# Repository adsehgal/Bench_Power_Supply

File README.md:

<!--  -->

# _Bench Power Supply PCB_

This repo contains project files for a bench top power supply I designed for my home lab.

## _Requirements:_

- **Small** for crammed work spaces
- **Adjustable** and designed to **store values** on each power cycle
- **2 layer** board - V2.0 bumped to 4 layer
- **Digitally controlled** - no mechanical parts
- Clear **annunciators**
- Uses an external AC-DC converter
- At least a **2A max** load
- Cover most logic levels
- _Possibly have preset buttons_

## Built With:

#### V1.0:

- [KiCad](https://kicad-pcb.org/) - Schematic capture and layout V1.0
- [VS Code | PlatformIO](https://code.visualstudio.com/) - Used to develop firmware V1.0
- [Fusion 360](https://www.autodesk.com/education/edu-software/overview) - Used to design 3-D models for packages

#### V2.0:

- [Altium Designer](https://www.altium.com/) - Schematic capture and layout V2.0
- [STM32CubeIDE](https://www.st.com/en/development-tools/stm32cubeide.html) - Used to develop firmware V2.0

## Notes:

- The PCB uses a 5/5mil DRC constraint
- The top of the PCB acts as the product face plate

## Firmware Changes:

| Change Type          | V 1.0     | V2.0       |
| -------------------- | --------- | ---------- |
| MCU Architecture     | 8-bit AVR | 32-bit ARM |
| User Input Handling  | Polling   | Interrupts |
| Analog Readings      | Polling   | DMA        |
| Serial Communication | None      | Added      |
| Operating System     | None      | FREERTOS   |
|                      |           |            |

## Hardware Changes:

| Change Type       | V 1.0             | V2.0              |
| ----------------- | ----------------- | ----------------- |
| MCU Selection     | ATMega 328p       | STM32F401RB       |
| Digi Pot          | MCP4023 - Up/Down | MCP4018 - I2C     |
| Inductor Seletion | 4.7µH - 7A        | 4.7µH - 4A        |
| PCB Stackup       | 2-layer           | 4-layer           |
| User Input Buffer | None              | Schmitt triggered |
| Analog Buffers    | LM358 - Not RRIO  | TLV271 - RRIO     |
| MCU VDD           | Not always on     | Always On         |
| OLED Reset        | None              | Added             |
|                   |                   |                   |

## Authors

- **Aditya Sehgal** - _PCB Layout, Firmware, 3-D Modelling_ - [Adsehgal](https://github.com/adsehgal)

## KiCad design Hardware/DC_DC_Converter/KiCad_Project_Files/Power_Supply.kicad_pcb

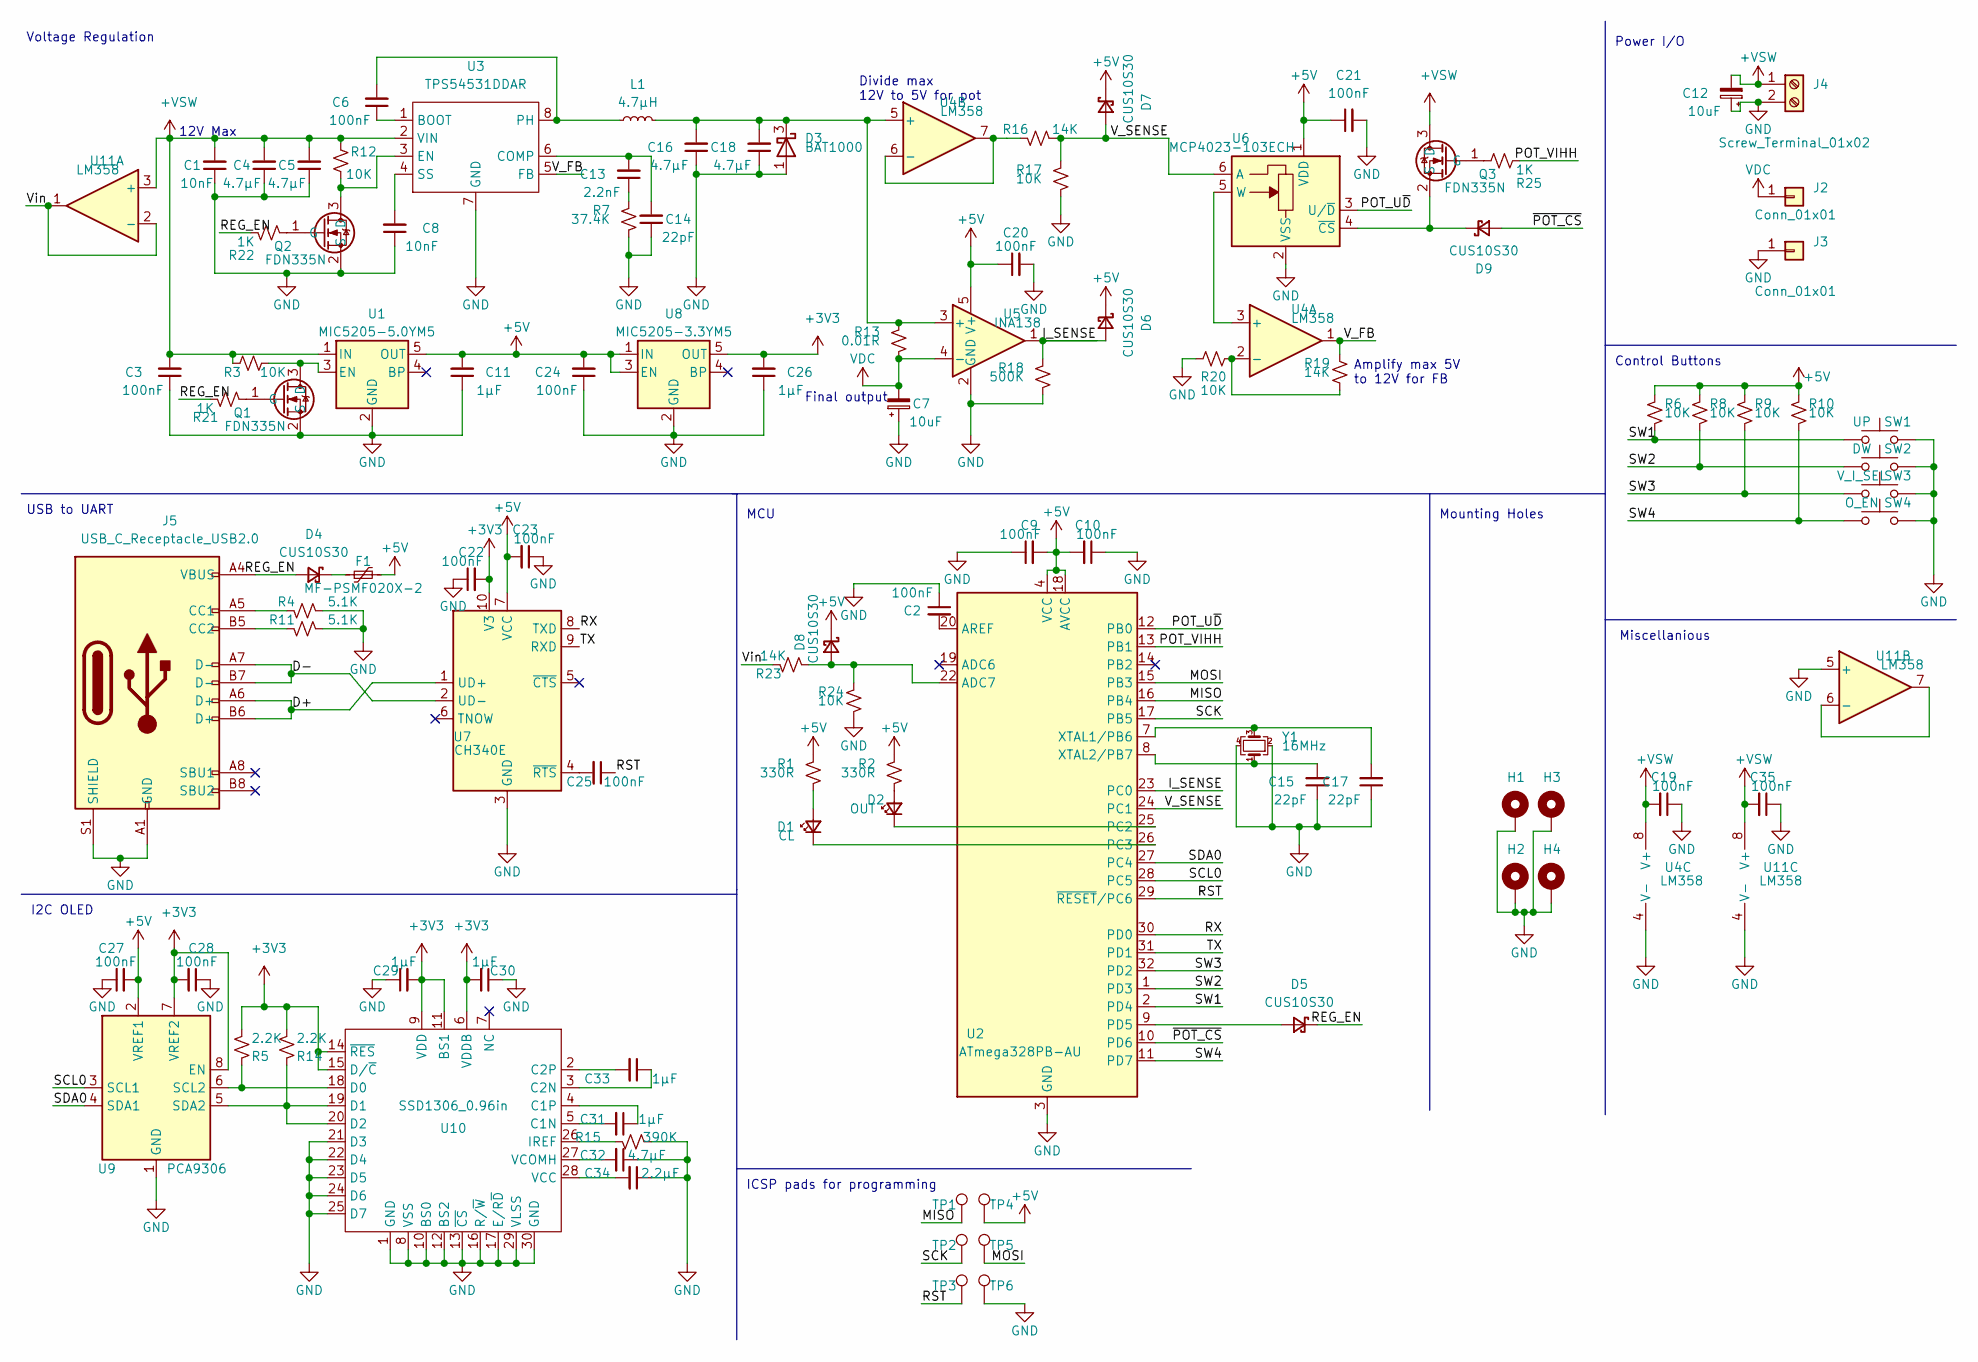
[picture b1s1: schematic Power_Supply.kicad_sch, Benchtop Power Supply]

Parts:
C1, C8: 10nF; C_0805_2012Metric
C2, C3, C6, C9, C10, C19, C20, C21, C22, C23, C24, C25, C27, C28, C35: 100nF; C_0805_2012Metric
C4, C5, C16, C18, C32: 4.7µF; C_0805_2012Metric
C7, C12: 10uF; C_Elec_5x5.4
C11, C26, C29, C30, C31, C33: 1µF; C_0805_2012Metric
C13: 2.2nF; C_0805_2012Metric
C14, C15, C17: 22pF; C_0805_2012Metric
C34: 2.2µF; C_0805_2012Metric
D1: CL; LED_0805_2012Metric
D2: OUT; LED_0805_2012Metric
D3: BAT1000; TSOT-23
D4, D5, D6, D7, D8, D9: CUS10S30; D_SOD-323
F1: MF-PSMF020X-2; Fuse_0805_2012Metric_Castellated
H1, H2, H3, H4: MountingHole_Pad; MountingHole_2.2mm_M2_ISO7380_Pad
J2, J3: Conn_01x01; Binding_Post
J4: Screw_Terminal_01x02; Altech_AK300_1x02_P5.00mm_45-Degree
J5: USB_C_Receptacle_USB2.0; USB_C_Receptacle_HRO_TYPE-C-31-M-12
L1: 4.7µH; L_Bourns_SRR1260
Q1, Q2, Q3: FDN335N; SOT-23
R1, R2: 330R; R_0805_2012Metric
R3, R6, R8, R9, R10, R12, R17, R20, R24: 10K; R_0805_2012Metric
R4, R11: 5.1K; R_0805_2012Metric
R5, R14: 2.2K; R_0805_2012Metric
R7: 37.4K; R_0805_2012Metric
R13: 0.01R; R_1020_2550Metric
R15: 390K; R_0805_2012Metric
R16, R19, R23: 14K; R_0805_2012Metric
R18: 500K; R_0805_2012Metric
R21, R22, R25: 1K; R_0805_2012Metric
SW1: UP; SW_SPST_TL3342
SW2: DW; SW_SPST_TL3342
SW3: V_I_SEL; SW_SPST_TL3342
SW4: O_EN; SW_SPST_TL3342
TP1, TP2, TP3, TP4, TP5, TP6: TestPoint; TestPoint_Pad_D1.0mm
U1: MIC5205-5.0YM5; SOT-23-5
U2: ATmega328PB-AU; TQFP-32_7x7mm_P0.8mm
U3: TPS54531DDAR; SOIC-8-1EP_3.9x4.9mm_P1.27mm_EP2.514x3.2mm
U4, U11: LM358; MSOP-8_3x3mm_P0.65mm
U5: INA138; SOT-23-5
U6: MCP4023-103ECH; SOT-23-6
U7: CH340E; MSOP-10_3x3mm_P0.5mm
U8: MIC5205-3.3YM5; SOT-23-5
U9: PCA9306; VSSOP-8_2.3x2mm_P0.5mm
U10: SSD1306_0.96in
Y1: 16MHz; Crystal_SMD_SeikoEpson_TSX3225-4Pin_3.2x2.5mm

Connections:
+3V3: C22.2, C26.2, C28.2, C29.2, C30.2, R5.1, R14.1, U7.10 (V3), U8.5 (OUT), U9.7 (VREF2), U9.8 (EN), U10.6 (VDDB), U10.9 (VDD), U10.11 (BS1), U10.14 (~RES), U10.15 (D/~C)
+5V: C9.2, C10.2, C11.2, C20.1, C21.1, C23.2, C24.2, C27.2, D6.1 (K), D7.1 (K), D8.1 (K), F1.2, R1.2, R2.2, R6.1, R8.1, R9.1, R10.1, TP4.1, U1.5 (OUT), U2.4 (VCC), U2.6 (VCC), U2.18 (AVCC), U5.5 (V+), U6.1 (VDD), U7.7 (VCC), U8.1 (IN), U8.3 (EN), U9.2 (VREF1)
+VSW: C1.2, C3.2, C4.2, C5.2, C12.2, C19.2, C35.2, J4.1, Q3.3 (D), R3.2, R12.2, U1.1 (IN), U3.2 (VIN), U4.8 (V+), U11.3 (+), U11.8 (V+)
/D+: J5.A6 (D+), J5.B6 (D+), U7.1 (UD+)
/D-: J5.A7 (D-), J5.B7 (D-), U7.2 (UD-)
/I_SENSE: D6.2 (A), R18.2, U2.23 (PC0), U5.1
/MISO: TP1.1, U2.16 (PB4)
/MOSI: TP5.1, U2.15 (PB3)
/POT_U~D: U2.12 (PB0), U6.3 (U/~D)
/POT_VIHH: R25.2, U2.13 (PB1)
/REG_EN: D4.2 (A), D5.1 (K), J5.A4 (VBUS), J5.A9 (VBUS), J5.B4 (VBUS), J5.B9 (VBUS), R21.2, R22.2
/RST: C25.1, TP3.1, U2.29 (~RESET~/PC6)
/RX: U2.30 (PD0), U7.8 (TXD)
/SCK: TP2.1, U2.17 (PB5)
/SCL0: U2.28 (PC5), U9.3 (SCL1)
/SDA0: U2.27 (PC4), U9.4 (SDA1)
/SW1: R6.2, SW1.1, U2.2 (PD4)
/SW2: R8.2, SW2.1, U2.1 (PD3)
/SW3: R9.2, SW3.1, U2.32 (PD2)
/SW4: R10.2, SW4.1, U2.11 (PD7)
/TX: U2.31 (PD1), U7.9 (RXD)
/V_FB: R19.1, U3.5 (FB), U4.1
/V_SENSE: D7.2 (A), R16.1, R17.2, U2.24 (PC1), U6.6 (A)
/Vin: R23.1, U11.1, U11.2 (-)
/~POT_CS: D9.2 (A), U2.10 (PD6)
GND: C1.1, C2.1, C3.1, C4.1, C5.1, C7.1, C8.1, C9.1, C10.1, C11.1, C12.1, C14.1, C15.1, C16.1, C17.1, C18.1, C19.1, C20.2, C21.2, C22.1, C23.1, C24.1, C26.1, C27.1, C28.1, C29.1, C30.1, C32.1, C34.1, C35.1, D3.1, H1.1, H2.1, H3.1, H4.1, J3.1, J4.2, J5.A1 (GND), J5.A12 (GND), J5.B1 (GND), J5.B12 (GND), J5.S1 (SHIELD), Q1.2 (S), Q2.2 (S), R4.1, R7.1, R11.1, R15.1, R17.1, R18.1, R20.2, R24.1, SW1.2, SW2.2, SW3.2, SW4.2, TP6.1, U1.2 (GND), U2.3 (GND), U2.5 (GND), U2.21 (GND), U3.7 (GND), U3.9 (GND), U4.4 (V-), U5.2 (GND), U6.2 (VSS), U7.3 (GND), U8.2 (GND), U9.1 (GND), U10.1 (GND), U10.8 (VSS), U10.10 (BS0), U10.12 (BS2), U10.13 (~CS), U10.16 (R/~W), U10.17 (E/R~D), U10.21 (D3), U10.22 (D4), U10.23 (D5), U10.24 (D6), U10.25 (D7), U10.29 (VLSS), U10.30 (GND), U11.4 (V-), U11.5 (+), Y1.2, Y1.4
unnamed: C2.2, U2.20 (AREF)
unnamed: C6.1, U3.1 (BOOT)
unnamed: C6.2, L1.1, U3.8 (PH)
unnamed: C8.2, U3.4 (SS)
unnamed: C13.1, R7.2
unnamed: C13.2, C14.2, U3.6 (COMP)
unnamed: C15.2, U2.8 (XTAL2/PB7), Y1.1
unnamed: C16.2, C18.2, D3.3, L1.2, R13.2, U4.5 (+), U5.3 (+)
unnamed: C17.2, U2.7 (XTAL1/PB6), Y1.3
unnamed: C25.2, U7.4 (~RTS)
unnamed: C31.1, U10.4 (C1P)
unnamed: C31.2, U10.5 (C1N)
unnamed: C32.2, U10.27 (VCOMH)
unnamed: C33.1, U10.3 (C2N)
unnamed: C33.2, U10.2 (C2P)
unnamed: C34.2, U10.28 (VCC)
unnamed: D1.1 (K), U2.26 (PC3)
unnamed: D1.2 (A), R1.1
unnamed: D2.1 (K), U2.25 (PC2)
unnamed: D2.2 (A), R2.1
unnamed: D4.1 (K), F1.1
unnamed: D5.2 (A), U2.9 (PD5)
unnamed: D8.2 (A), R23.2, R24.2, U2.22 (ADC7)
unnamed: D9.1 (K), Q3.2 (S), U6.4 (~CS)
unnamed: J5.A5 (CC1), R4.2
unnamed: J5.B5 (CC2), R11.2
unnamed: Q1.1 (G), R21.1
unnamed: Q1.3 (D), R3.1, U1.3 (EN)
unnamed: Q2.1 (G), R22.1
unnamed: Q2.3 (D), R12.1, U3.3 (EN)
unnamed: Q3.1 (G), R25.1
unnamed: R5.2, U9.6 (SCL2), U10.18 (D0)
unnamed: R14.2, U9.5 (SDA2), U10.19 (D1), U10.20 (D2)
unnamed: R15.2, U10.26 (IREF)
unnamed: R16.2, U4.6 (-), U4.7
unnamed: R19.2, R20.1, U4.2 (-)
unnamed: U4.3 (+), U6.5 (W)
unnamed: U11.6 (-), U11.7
VDC: C7.2, J2.1, R13.1, U5.4 (-)

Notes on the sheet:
Voltage Regulation
USB to UART
I2C OLED
12V Max
MCU
ICSP pads for programming
Final output
Divide max 12V to 5V for pot
Amplify max 5V to 12V for FB
Mounting Holes
Power I/O
Control Buttons
Miscellanious

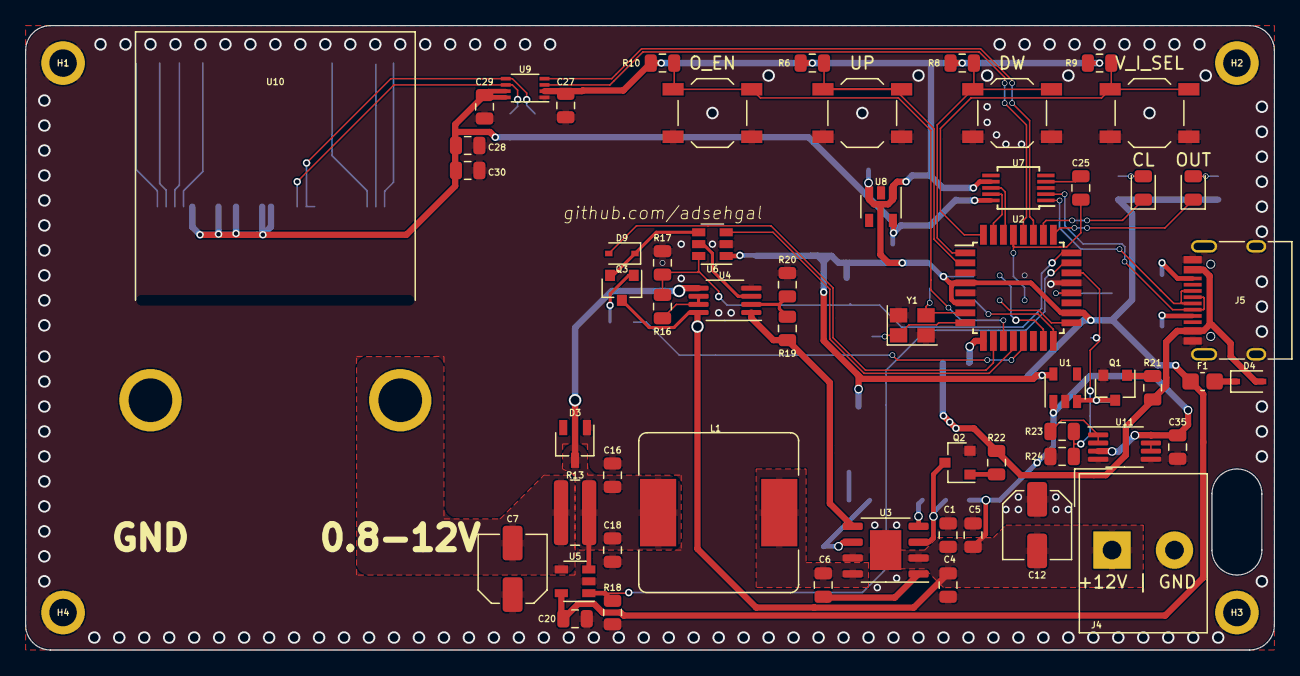
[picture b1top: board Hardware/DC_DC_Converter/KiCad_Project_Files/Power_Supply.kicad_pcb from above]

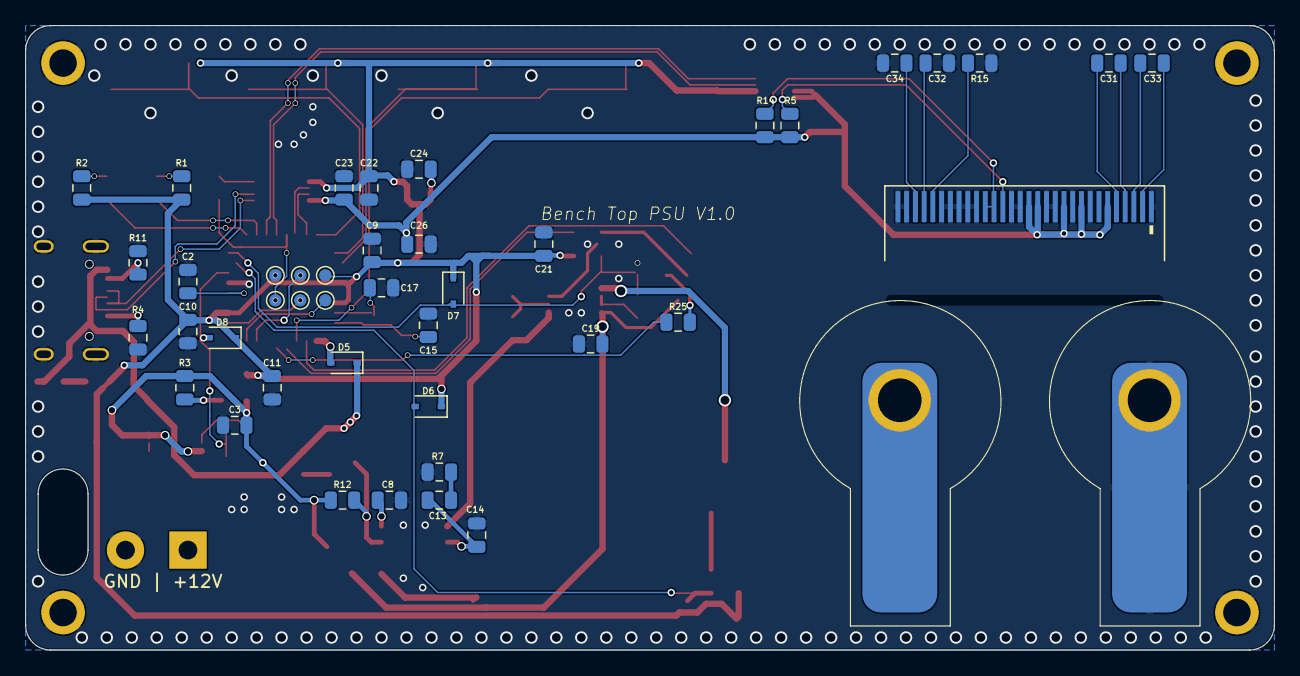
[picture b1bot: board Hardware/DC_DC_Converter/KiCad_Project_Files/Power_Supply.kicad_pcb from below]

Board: 2 copper layers, 100.0 x 50.0 mm, 104 parts (41 on the bottom side), 65 nets.

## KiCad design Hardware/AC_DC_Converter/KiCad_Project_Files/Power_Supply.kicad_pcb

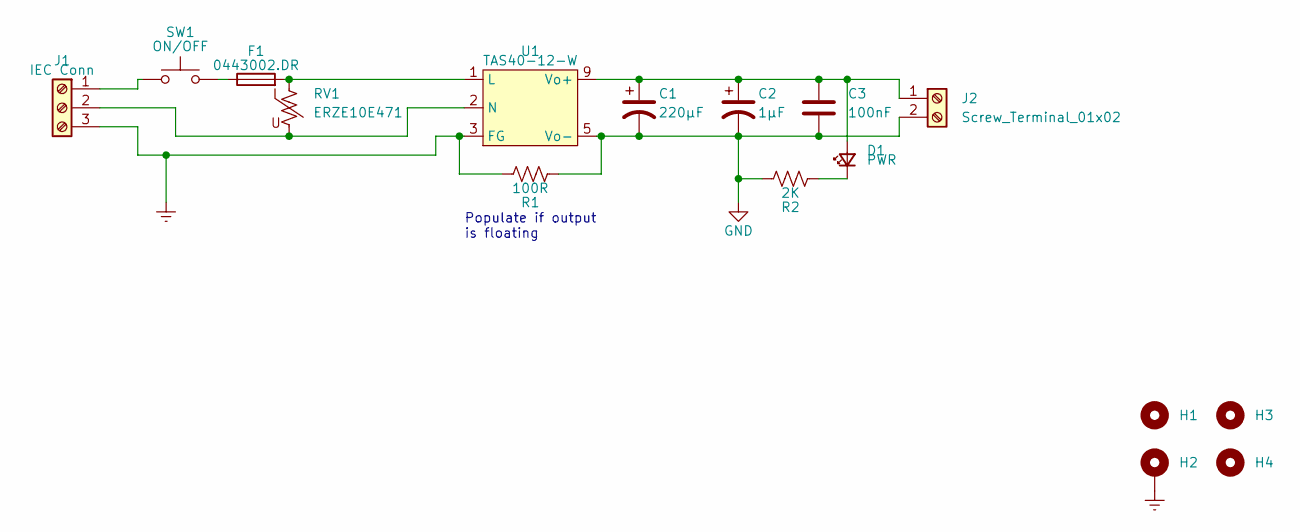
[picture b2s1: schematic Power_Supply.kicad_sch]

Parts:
C1: 220µF; CP_Elec_8x10.5
C2: 1µF; CP_Elec_4x5.4
C3: 100nF; C_0805_2012Metric
D1: PWR; LED_0805_2012Metric_Castellated
F1: 0443002.DR; LittleFuse-0443002
H1, H3, H4: MountingHole; MountingHole_2.2mm_M2_DIN965_Pad
H2: Earth; MountingHole_2.2mm_M2_DIN965_Pad
J1: IEC Conn; ACT3KD-03BT3B018
J2: Screw_Terminal_01x02; Altech_AK300_1x02_P5.00mm_45-Degree
R1: 100R; R_0805_2012Metric
R2: 2K; R_0805_2012Metric
RV1: ERZE10E471; RV_Disc_D12mm_W3.9mm_P7.5mm
SW1: ON/OFF; BPT
U1: TAS40-12-W

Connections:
Earth: H2.1, J1.3, R1.2, U1.3 (FG)
GND: C1.2, C2.2, C3.2, J2.2, R1.1, R2.2, U1.5 (Vo-)
unnamed: C1.1, C2.1, C3.1, D1.2 (A), J2.1, U1.9 (Vo+)
unnamed: D1.1 (K), R2.1
unnamed: F1.1, SW1.2
unnamed: F1.2, RV1.1, U1.1 (L)
unnamed: J1.1, SW1.1
unnamed: J1.2, RV1.2, U1.2 (N)

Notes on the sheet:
Populate if output is floating

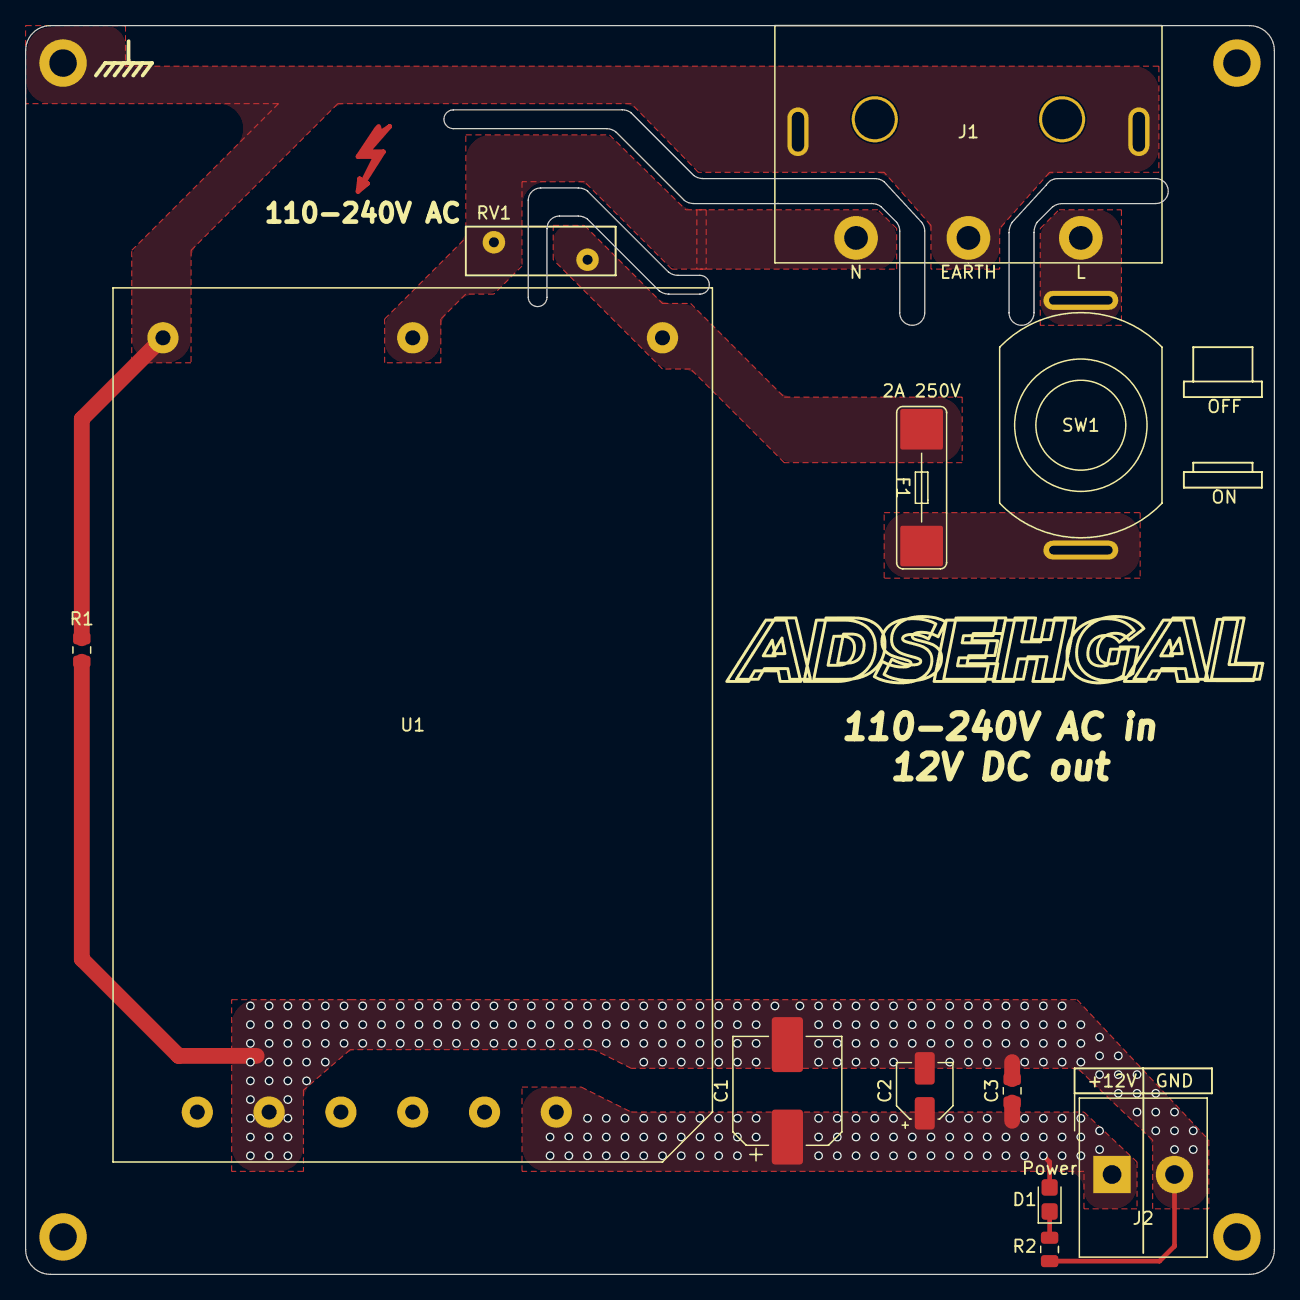
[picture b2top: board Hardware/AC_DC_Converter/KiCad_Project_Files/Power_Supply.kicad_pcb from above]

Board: 2 copper layers, 100.0 x 100.0 mm, 16 parts (0 on the bottom side), 8 nets.

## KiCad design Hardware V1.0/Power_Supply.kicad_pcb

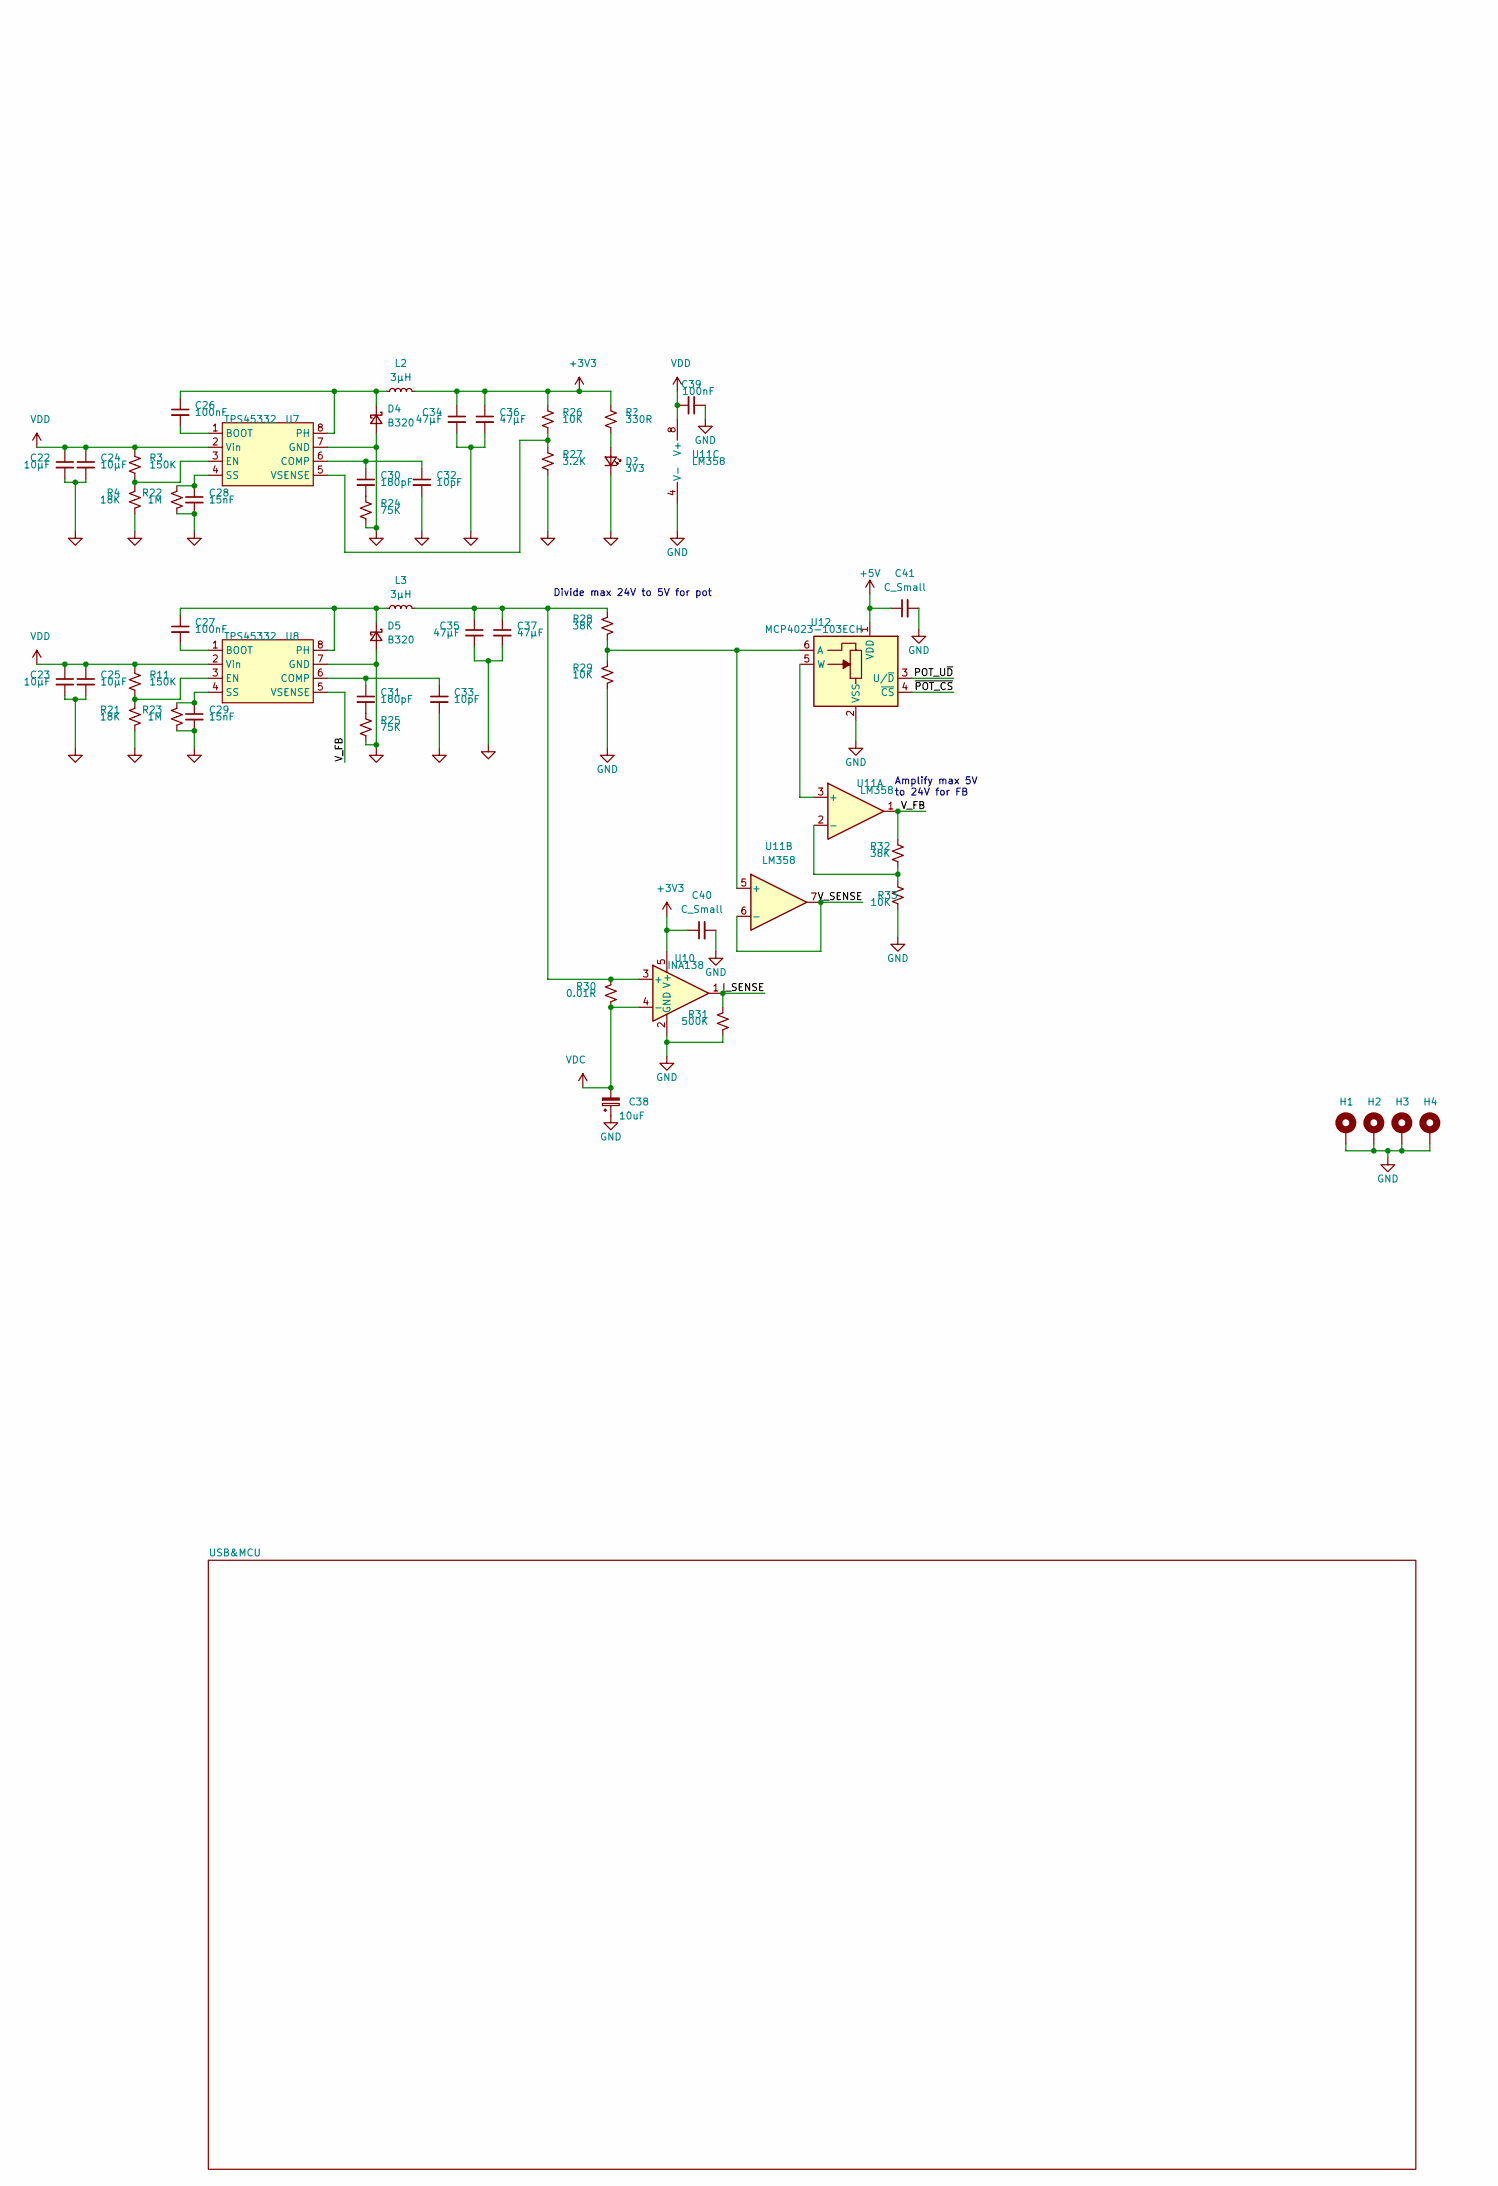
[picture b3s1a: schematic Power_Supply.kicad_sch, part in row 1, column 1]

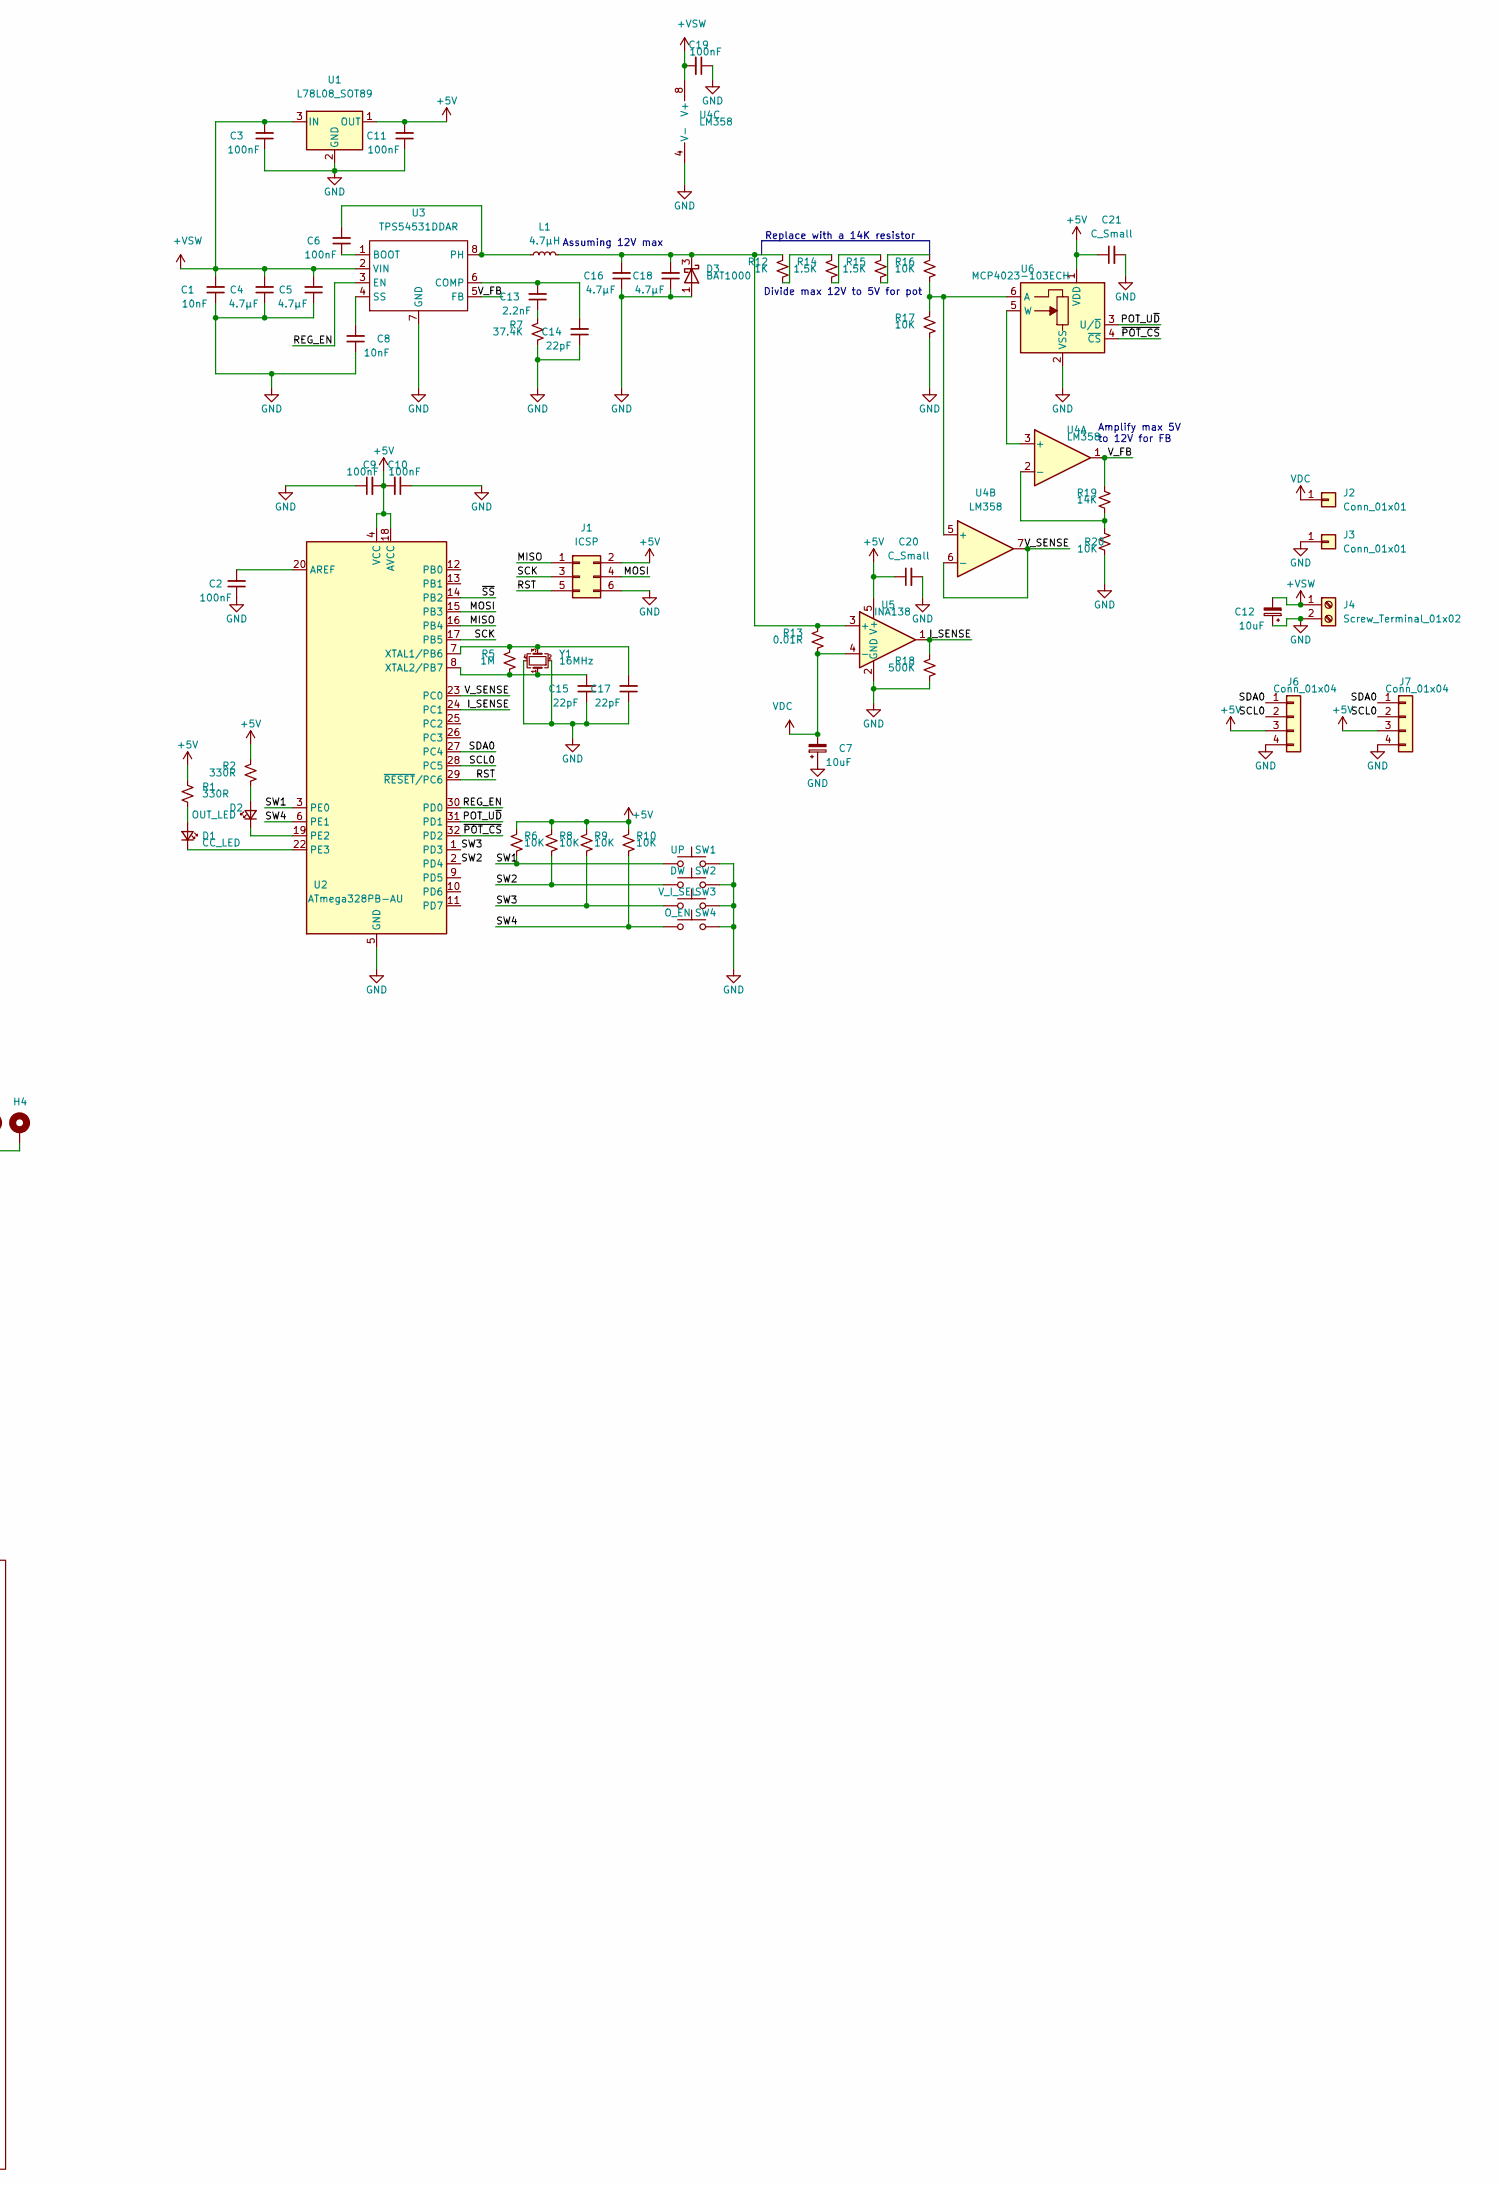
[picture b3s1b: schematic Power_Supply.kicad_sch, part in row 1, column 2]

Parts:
C1, C8: 10nF; C_0805_2012Metric
C2, C3, C6, C9, C10, C11, C19, C26, C27, C39: 100nF; C_0805_2012Metric
C4, C5, C16, C18: 4.7µF; C_0805_2012Metric
C7, C12, C38: 10uF; C_Elec_5x5.4
C13: 2.2nF; C_0805_2012Metric
C14, C15, C17: 22pF; C_0805_2012Metric
C20, C21, C40, C41: C_Small; C_0805_2012Metric
C22, C23, C24, C25: 10μF; C_0805_2012Metric
C28, C29: 15nF; C_0805_2012Metric
C30, C31: 180pF; C_0805_2012Metric
C32, C33: 10pF; C_0805_2012Metric
C34, C35, C36, C37: 47µF; C_0805_2012Metric
D1: CC_LED; LED_0805_2012Metric
D2: OUT_LED; LED_0805_2012Metric
D3: BAT1000; TSOT-23
D4, D5: B320; D_SMA
H1, H2, H3, H4: MountingHole_Pad; MountingHole_2.2mm_M2_ISO7380_Pad
J1: ICSP; PinHeader_2x03_P2.54mm_Vertical
J2, J3: Conn_01x01; Binding_Post
J4: Screw_Terminal_01x02; Altech_AK300_1x02_P5.00mm_45-Degree
J6, J7: Conn_01x04; PinHeader_1x04_P2.54mm_Vertical
L1: 4.7µH; L_Bourns_SRR1260
L2, L3: 3μH; L_Sunlord_MWSA0518_5.4x5.2mm
R1, R2: 330R; R_0805_2012Metric
R3, R11: 150K; R_0805_2012Metric
R4, R21: 18K; R_0805_2012Metric
R5, R22, R23: 1M; R_0805_2012Metric
R6, R8, R9, R10, R16, R17, R20, R26, R29, R33: 10K; R_0805_2012Metric
R7: 37.4K; R_0805_2012Metric
R12: 1K; R_0805_2012Metric
R13, R30: 0.01R; R_1020_2550Metric
R14, R15: 1.5K; R_0805_2012Metric
R18, R31: 500K; R_0805_2012Metric
R19: 14K; R_0805_2012Metric
R24, R25: 75K; R_0805_2012Metric
R27: 3.2K; R_0805_2012Metric
R28, R32: 38K; R_0805_2012Metric
SW1: UP; SW_SPST_TL3342
SW2: DW; SW_SPST_TL3342
SW3: V_I_SEL; SW_SPST_TL3342
SW4: O_EN; SW_SPST_TL3342
U1: L78L08_SOT89; SOT-89-3
U2: ATmega328PB-AU; TQFP-32_7x7mm_P0.8mm
U3: TPS54531DDAR; SOIC-8-1EP_3.9x4.9mm_P1.27mm_EP2.514x3.2mm
U4, U11: LM358; SOIC-8_3.9x4.9mm_P1.27mm
U5, U10: INA138; SOT-23-5
U6, U12: MCP4023-103ECH; SOT-23-6
U7, U8: TPS45332; SOP-8-1EP_4.57x4.57mm_P1.27mm_EP4.57x4.45mm
Y1: 16MHz; Crystal_SMD_SeikoEpson_TSX3225-4Pin_3.2x2.5mm_HandSoldering

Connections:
+3V3: C34.1, C36.1, C40.1, L2.2, R26.1, U10.5 (V+); also elsewhere on the board
+5V: C9.2, C10.2, C11.2, C20.1, C21.1, C41.1, J1.2, J6.3, J7.3, R1.2, R2.2, R6.1, R8.1, R9.1, R10.1, U1.1 (OUT), U2.4 (VCC), U2.18 (AVCC), U5.5 (V+), U6.1 (VDD), U12.1 (VDD)
+VSW: C1.2, C3.2, C4.2, C5.2, C12.2, C19.2, J4.1, U1.3 (IN), U3.2 (VIN), U4.8 (V+)
/I_SENSE: R18.2, R31.2, U2.24 (PC1), U5.1, U10.1
/MISO: J1.1, U2.16 (PB4)
/MOSI: J1.4, U2.15 (PB3)
/POT_U~D: U2.31 (PD1), U6.3 (U/~D), U12.3 (U/~D)
/REG_EN: U2.30 (PD0), U3.3 (EN)
/RST: J1.5, U2.29 (~RESET~/PC6)
/SCK: J1.3, U2.17 (PB5)
/SCL0: J6.2, J7.2, U2.28 (PC5)
/SDA0: J6.1, J7.1, U2.27 (PC4)
/SW1: R6.2, SW1.1, U2.3 (PE0)
/SW2: R8.2, SW2.1, U2.2 (PD4)
/SW3: R9.2, SW3.1, U2.1 (PD3)
/SW4: R10.2, SW4.1, U2.6 (PE1)
/V_FB: R19.1, R32.1, U3.5 (FB), U4.1, U8.5 (VSENSE), U11.1
/V_SENSE: U2.23 (PC0), U4.6 (-), U4.7, U11.6 (-), U11.7
/~POT_CS: U2.32 (PD2), U6.4 (~CS), U12.4 (~CS)
/~SS: U2.14 (PB2)
GND: C1.1, C2.1, C3.1, C4.1, C5.1, C7.1, C8.1, C9.1, C10.1, C11.1, C12.1, C14.1, C15.1, C16.1, C17.1, C18.1, C19.1, C20.2, C21.2, C22.2, C23.2, C24.2, C25.2, C28.2, C29.2, C32.2, C33.2, C34.2, C35.2, C36.2, C37.2, C38.1, C39.1, C40.2, C41.2, D3.1, D4.2 (A), D5.2 (A), H1.1, H2.1, H3.1, H4.1, J1.6, J3.1, J4.2, J6.4, J7.4, R4.2, R7.1, R17.1, R18.1, R20.1, R21.2, R22.2, R23.2, R24.2, R25.2, R27.2, R29.1, R31.1, R33.1, SW1.2, SW2.2, SW3.2, SW4.2, U1.2 (GND), U2.5 (GND), U2.21 (GND), U3.7 (GND), U3.9 (GND), U4.4 (V-), U5.2 (GND), U6.2 (VSS), U7.7 (GND), U8.7 (GND), U10.2 (GND), U11.4 (V-), U12.2 (VSS), Y1.2, Y1.4
unnamed: C2.2, U2.20 (AREF)
unnamed: C6.1, U3.1 (BOOT)
unnamed: C6.2, L1.1, U3.8 (PH)
unnamed: C8.2, U3.4 (SS)
unnamed: C13.1, R7.2
unnamed: C13.2, C14.2, U3.6 (COMP)
unnamed: C15.2, R5.1, U2.8 (XTAL2/PB7), Y1.1
unnamed: C16.2, C18.2, D3.3, L1.2, R12.2, R13.2, U5.3 (+)
unnamed: C17.2, R5.2, U2.7 (XTAL1/PB6), Y1.3
unnamed: C26.1, D4.1 (K), L2.1, U7.8 (PH)
unnamed: C26.2, U7.1 (BOOT)
unnamed: C27.1, D5.1 (K), L3.1, U8.8 (PH)
unnamed: C27.2, U8.1 (BOOT)
unnamed: C28.1, R22.1, U7.4 (SS)
unnamed: C29.1, R23.1, U8.4 (SS)
unnamed: C30.1, C32.1, U7.6 (COMP)
unnamed: C30.2, R24.1
unnamed: C31.1, C33.1, U8.6 (COMP)
unnamed: C31.2, R25.1
unnamed: C35.1, C37.1, L3.2, R28.2, R30.2, U10.3 (+)
unnamed: D1.1 (K), U2.22 (PE3)
unnamed: D1.2 (A), R1.1
unnamed: D2.1 (K), U2.19 (PE2)
unnamed: D2.2 (A), R2.1
unnamed: R3.2, R4.1, U7.3 (EN)
unnamed: R11.2, R21.1, U8.3 (EN)
unnamed: R12.1, R14.2
unnamed: R14.1, R15.2
unnamed: R15.1, R16.2
unnamed: R16.1, R17.2, U4.5 (+), U6.6 (A)
unnamed: R19.2, R20.2, U4.2 (-)
unnamed: R26.2, R27.1, U7.5 (VSENSE)
unnamed: R28.1, R29.2, U11.5 (+), U12.6 (A)
unnamed: R32.2, R33.2, U11.2 (-)
unnamed: U4.3 (+), U6.5 (W)
unnamed: U11.3 (+), U12.5 (W)
VDC: C7.2, C38.2, J2.1, R13.1, R30.1, U5.4 (-), U10.4 (-)
VDD: C22.1, C23.1, C24.1, C25.1, C39.2, R3.1, R11.1, U7.2 (Vin), U8.2 (Vin), U11.8 (V+)

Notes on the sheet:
Divide max 24V to 5V for pot
Amplify max 5V to 24V for FB
Assuming 12V max
Replace with a 14K resistor
Divide max 12V to 5V for pot
Amplify max 5V to 12V for FB

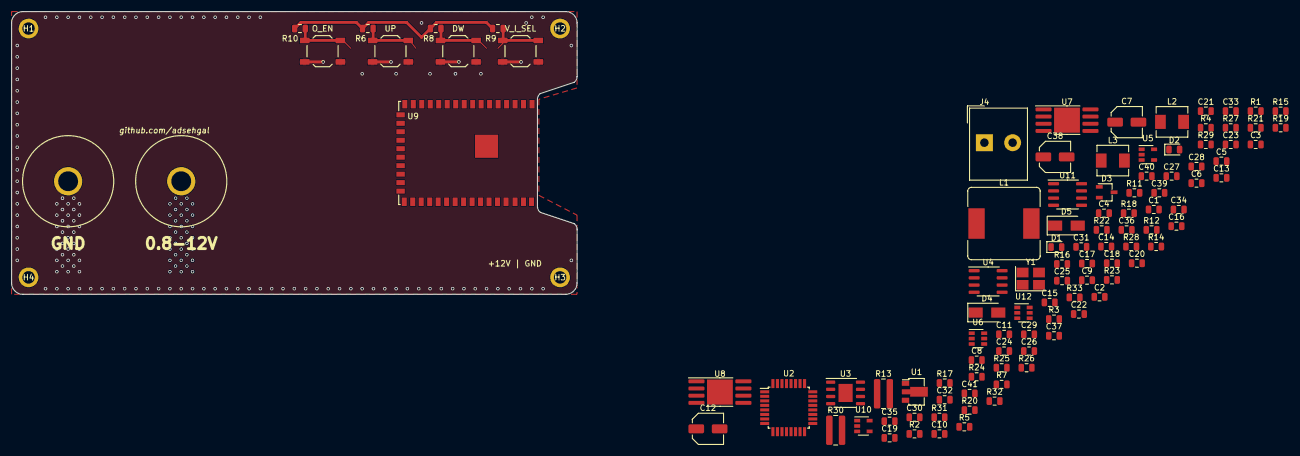
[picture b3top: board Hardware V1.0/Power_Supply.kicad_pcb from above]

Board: 2 copper layers, 100.0 x 50.0 mm, 106 parts (0 on the bottom side), 53 nets.

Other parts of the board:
U9: ESP32-S2-WROVER-I; ESP32-S2-WROVER

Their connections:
+3V3: U9.2 (3V3); also elsewhere on the board
unnamed: U9.1 (GND), U9.26 (GND), U9.42 (GND), U9.43 (GND)
